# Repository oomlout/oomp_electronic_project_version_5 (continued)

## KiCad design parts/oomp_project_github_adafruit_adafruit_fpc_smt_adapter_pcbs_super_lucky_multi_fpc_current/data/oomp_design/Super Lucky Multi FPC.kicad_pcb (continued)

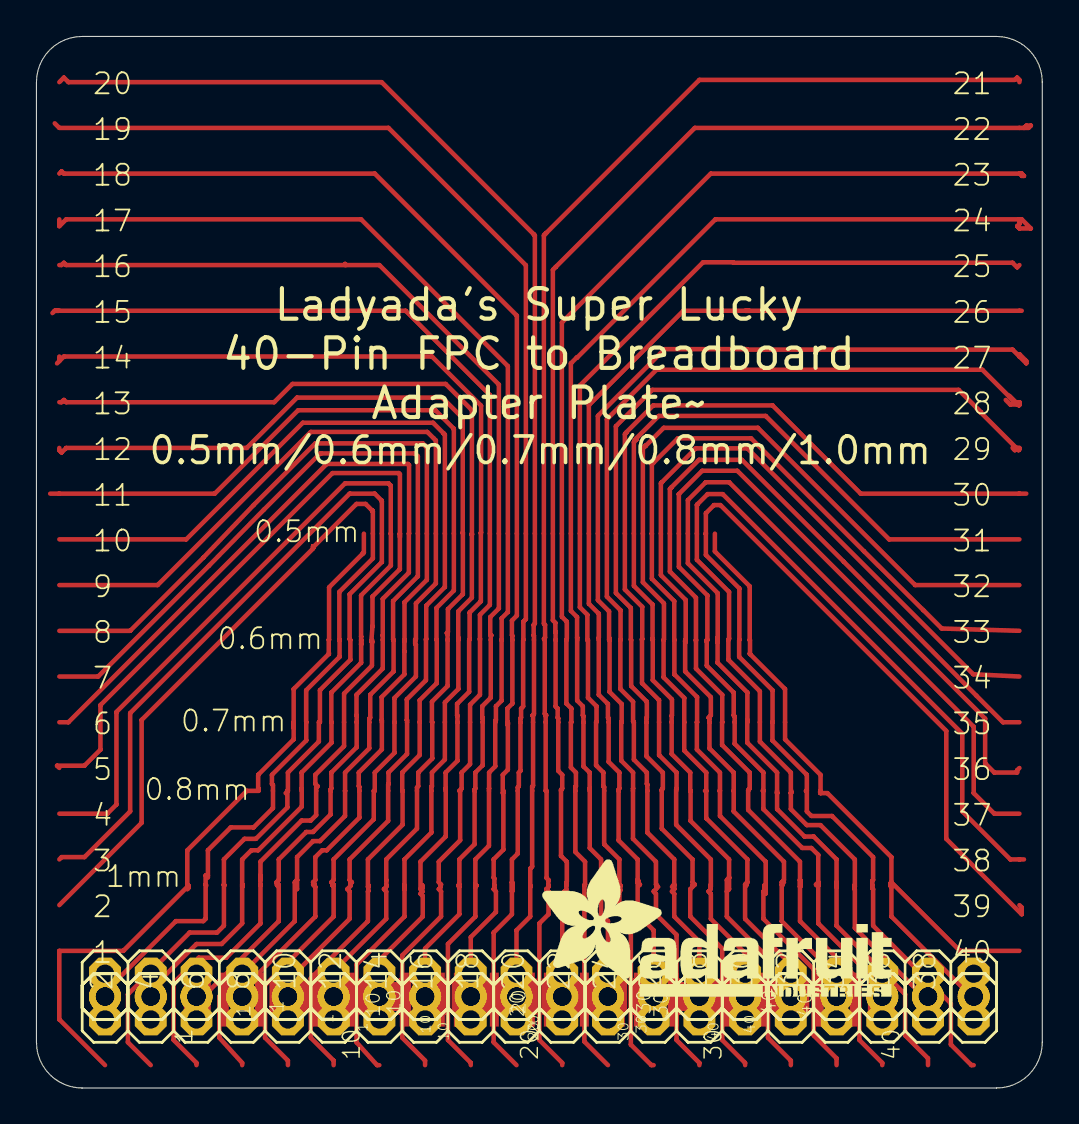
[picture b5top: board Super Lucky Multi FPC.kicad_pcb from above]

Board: 16 copper layers, 55.9 x 58.4 mm, 9 parts (0 on the bottom side), 40 nets.

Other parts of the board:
U$5: ADAFRUIT_TEXT_20MM

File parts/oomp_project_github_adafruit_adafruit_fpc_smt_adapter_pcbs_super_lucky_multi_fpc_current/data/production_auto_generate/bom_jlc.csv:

Comment,Designator,Footprint,LCSC Part #
,"JP2,JP3",Super Lucky Multi FPC-import-fps:1X20-BIG,C50981
,JP1,Super Lucky Multi FPC-import-fps:2X20-BIG,
,U$5,Super Lucky Multi FPC-import-fps:ADAFRUIT_TEXT_20MM,
PINHD-1X40-0.5MM,CON1,Super Lucky Multi FPC-import-fps:1X40-0.5MM,C2337
PINHD-1X40-0.6MM,U$1,Super Lucky Multi FPC-import-fps:1X40-0.6MM,
PINHD-1X40-0.7MM,U$2,Super Lucky Multi FPC-import-fps:1X40-0.7MM,
PINHD-1X40-0.8MM,U$3,Super Lucky Multi FPC-import-fps:1X40-0.8MM,
PINHD-1X40-1MM,U$4,Super Lucky Multi FPC-import-fps:1X40-1MM,
